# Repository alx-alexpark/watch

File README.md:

# GPS-Synchronized Watch
A nRF52840-based smartwatch that synchronizes its time from GPS satelites, featuring a waterproof enclosure and month-long battery life.

## Why I made this
Commonly used time synchronization methods such as NTP commonly used by smartwatches only provide accuracy of around 5-50ms, which is honestly not that good. GPS time is accurate to 10-50 nanoseconds, which is very good. I also care a lot about privacy so I wanted to make an air-gapped smartwatch that still is able to get very accurate time.

## Design files
[View PCB/Schematics on KiCanvas](https://kicanvas.org/?repo=https%3A%2F%2Fgithub.com%2Falx-alexpark%2Fwatch%2Ftree%2Fmain%2Fpcb) \
[View CAD on OnShape](https://cad.onshape.com/documents/4c7ff3da2943e425ef5063a9/w/a0d315951a28c31d027d9c75/e/9f56870fde0bf2563f4cad87?renderMode=0&uiState=6a2ecfbd296c1803119f765e)

## BOM
| Value | Qty | Link |
|-------|-----|------|
| DSGP.1575.18.4.A.02 | 1 | [Digikey](https://www.digikey.com/en/products/detail/taoglas-limited/DSGP-1575-18-4-A-02/8275269) |
| Adafruit Wireless Chg Module | 1 | [Digikey](https://www.adafruit.com/product/1901) |
| 100nF | 9 | [C1525](https://www.lcsc.com/product-detail/C1525.html) |
| 100pF | 1 | [C1546](https://www.lcsc.com/product-detail/C1546.html) |
| 12pF | 2 | [C1547](https://www.lcsc.com/product-detail/C1547.html) |
| 47nF | 1 | [C1622](https://www.lcsc.com/product-detail/C1622.html) |
| red | 1 | [C2286](https://www.lcsc.com/product-detail/C2286.html) |
| green | 1 | [C2297](https://www.lcsc.com/product-detail/C2297.html) |
| USBLC6-2SC6 | 1 | [C7519](https://www.lcsc.com/product-detail/C7519.html) |
| 4.7uF | 5 | [C19666](https://www.lcsc.com/product-detail/C19666.html) |
| 1.13k | 1 | [C22833](https://www.lcsc.com/product-detail/C22833.html) |
| nRF52840 | 1 | [C23186](https://www.lcsc.com/product-detail/C23186.html) |
| 100k | 1 | [C25741](https://www.lcsc.com/product-detail/C25741.html) |
| 10k | 3 | [C25744](https://www.lcsc.com/product-detail/C25744.html) |
| 1.5k | 4 | [C25867](https://www.lcsc.com/product-detail/C25867.html) |
| 22uF | 1 | [C45783](https://www.lcsc.com/product-detail/C45783.html) |
| 1uF | 5 | [C52923](https://www.lcsc.com/product-detail/C52923.html) |
| BQ24074RGT | 1 | [C54313](https://www.lcsc.com/product-detail/C54313.html) |
| RV-3028-C7 | 1 | [C3019759](https://www.lcsc.com/product-detail/C3019759.html) |
| 1A/1.8A | 1 | [C70082](https://www.lcsc.com/product-detail/C70082.html) |
| 10uH | 2 | [C88182](https://www.lcsc.com/product-detail/C88182.html) |
| 10uF | 1 | [C96446](https://www.lcsc.com/product-detail/C96446.html) |
| 15nH | 1 | [C98055](https://www.lcsc.com/product-detail/C98055.html) |
|  | 1 | [C127355](https://www.lcsc.com/product-detail/C127355.html) |
| LiPo (JST-PH Connector) | 1 | [C295747](https://www.lcsc.com/product-detail/C295747.html) |
| TPS63802DLAR | 1 | [C2845237](https://www.lcsc.com/product-detail/C2845237.html) |
| 91k | 1 | [C2906973](https://www.lcsc.com/product-detail/C2906973.html) |
| 4.12k | 2 | [C2930007](https://www.lcsc.com/product-detail/C2930007.html) |
| 511k | 1 | [C2930114](https://www.lcsc.com/product-detail/C2930114.html) |
| USB_C_Receptacle_USB2.0_14P | 1 | [C2988369](https://www.lcsc.com/product-detail/C2988369.html) |
| 1.18k | 1 | [C3016052](https://www.lcsc.com/product-detail/C3016052.html) |
| TPS2116DRL | 1 | [C3235557](https://www.lcsc.com/product-detail/C3235557.html) |
| MAX-M10S | 1 | [C4153167](https://www.lcsc.com/product-detail/C4153167.html) |
| 46.4k | 1 | [C5126026](https://www.lcsc.com/product-detail/C5126026.html) |
| 32MHz | 1 | [C5441424](https://www.lcsc.com/product-detail/C5441424.html) |
| 0.47uH | 1 | [C18221164](https://www.lcsc.com/product-detail/C18221164.html) |
| TPS7A20xxxDQN | 1 | [C46459900](https://www.lcsc.com/product-detail/C46459900.html) |

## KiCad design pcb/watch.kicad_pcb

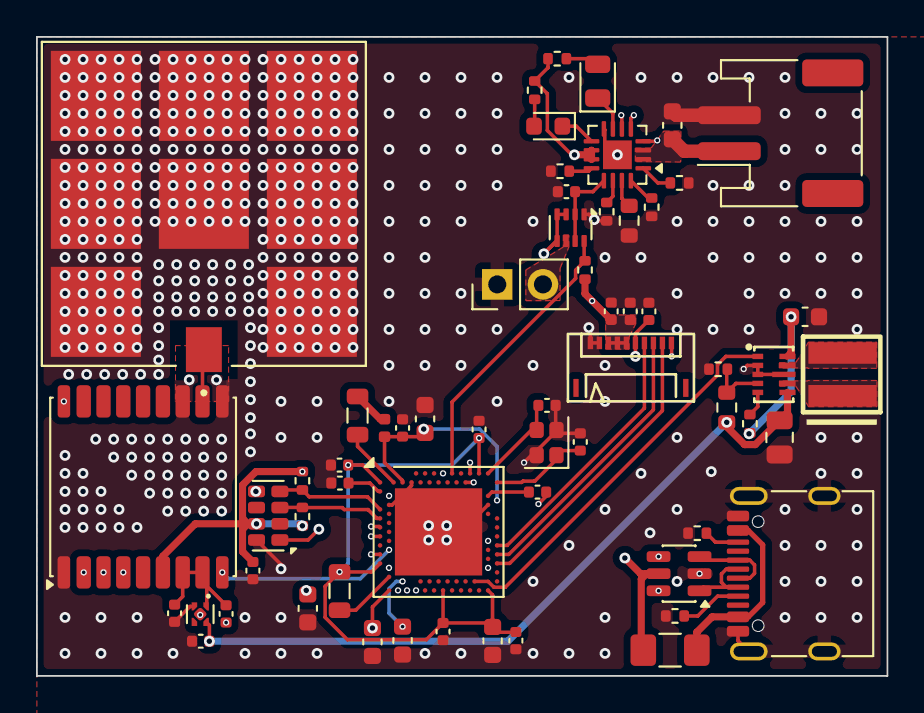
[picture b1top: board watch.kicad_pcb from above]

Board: 6 copper layers, 47.2 x 35.5 mm, 61 parts (0 on the bottom side), 59 nets.

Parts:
BT1: LiPo; JST_PH_S2B-PH-SM4-TB_1x02-1MP_P2.00mm_Horizontal
C1, C6, C7, C8, C9, C15, C25, C27, C28: 100nF; C_0402_1005Metric
C2, C10, C11, C12, C22: 4.7uF; C_0603_1608Metric
C3, C4: 12pF; C_0402_1005Metric
C5: 100pF; C_0402_1005Metric
C13, C18, C19, C21, C26: 1uF; C_0402_1005Metric
C14: 47nF; C_0603_1608Metric
C17: 10uF; C_0603_1608Metric
C20: 22uF; C_0805_2012Metric
D1: green; LED_0805_2012Metric
D2: red; LED_0603_1608Metric
DS1: 5034801000
E1: DSGP.1575.18.4.A.02; XCVR_DSGP.1575.18.4.A.02
F1: 1A/1.8A; Fuse_1206_3216Metric_Pad1.42x1.75mm_HandSolder
J1: USB_C_Receptacle_USB2.0_14P; USB_C_Receptacle_G-Switch_GT-USB-7010ASV
J2: Adafruit Wireless Chg Module; PinHeader_1x02_P2.54mm_Vertical
L1, L2: 10uH; L_0805_2012Metric
L3: 15nH; L_0402_1005Metric
L4: 0.47uH; XFL4015-471MEC
R1, R2: 4.12k; R_0402_1005Metric
R3: 511k; R_0603_1608Metric
R4: 91k; R_0402_1005Metric
R5: 100k; R_0402_1005Metric
R6: 1.18k; R_0402_1005Metric
R7, R8, R11, R12: 1.5k; R_0402_1005Metric
R9: 1.13k; R_0603_1608Metric
R10: 46.4k; R_0402_1005Metric
R15, R16, R17: 10k; R_0402_1005Metric
U1: nRF52840; Nordic_AQFN-73-1EP_7x7mm_P0.5mm
U2: USBLC6-2SC6; SOT-23-6
U3: MAX-M10S; ublox_MAX
U4: TPS63802DLAR
U5: TPS7A20xxxDQN; Texas_X2SON-4_1x1mm_P0.65mm
U6: BQ24074RGT; VQFN-16-1EP_3x3mm_P0.5mm_EP1.6x1.6mm
U8: RV-3028-C7; MicroCrystal_C7_SON-8_1.5x3.2mm_P0.9mm
U9: TPS2116DRL; SOT-583-8
Y1: 32MHz; Crystal_SMD_2016-4Pin_2.0x1.6mm

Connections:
+3V0_GPS: C15.1, C19.1, U3.7 (VCC_IO), U3.8 (VCC), U5.1 (OUT)
+3V3: C26.1, C27.1, C28.1, DS1.3 (EXTMODE), DS1.4 (VDD), DS1.5 (VDDA), R15.1, R16.1, R17.1, U3.6 (V_BCKP), U8.7 (VDD)
+3V3_ALT: C18.1, C20.1, R3.1, U4.6 (VOUT), U5.4 (IN)
+BATT: C11.1, C17.1, R5.1, R11.2, R12.2, U1.Y2 (VDDH), U4.10 (VIN), U6.10 (OUT), U6.11 (OUT)
/mcu/D+: U1.AD6 (D+), U2.4 (I/O2)
/mcu/D-: U1.AD4 (D-), U2.6 (I/O1)
/mcu/DEC4: C13.1, C14.1, L3.1, U1.B5 (DEC4), U1.E24 (DEC6)
/mcu/VDD_nRF: C1.1, C6.1, C8.1, C9.1, C10.1, L1.1, U1.A22 (VDD), U1.AD14 (VDD), U1.AD23 (VDD), U1.B1 (VDD), U1.W1 (VDD)
GND: BT1.2 (-), C1.2, C2.2, C3.1, C4.1, C5.2, C6.2, C7.2, C8.2, C9.2, C10.2, C11.2, C12.2, C13.2, C14.2, C15.2, C17.2, C18.2, C20.2, C21.2, C22.2, C25.2, C26.2, C27.2, C28.2, DS1.1 (VSSA), DS1.2 (VSS), E1.2, E1.3, E1.4, E1.5, E1.6, E1.7, E1.8, E1.9, J1.A1 (GND), J1.A12 (GND), J1.B1 (GND), J1.B12 (GND), J1.SH (SHIELD), J2.1, R1.2, R2.2, R4.2, R6.1, R7.1, R8.1, R9.1, R10.2, U1.B7 (VSS), U1.EP (VSS), U1.F2 (XL2/P0.01), U1.F23 (VSS_PA), U2.2 (GND), U3.1 (GND), U3.10 (GND), U3.12 (GND), U4.2 (MODE), U4.3 (AGND), U4.8 (GND), U5.2 (GND), U6.8 (VSS), U6.17 (VSS), U8.5 (VSS), U8.8 (EVI), U9.1 (GND), Y1.2 (G), Y1.4 (G)
LF_EXT_CLK: U1.D2 (XL1/P0.00), U8.1 (CLKOUT)
unnamed: BT1.1 (+), C22.1, U6.2 (BAT), U6.3 (BAT)
unnamed: C19.2, U5.5 (Pad)
unnamed: D1.2 (A), R11.1
unnamed: D1.1 (K), U6.7 (~PGOOD)
unnamed: D2.2 (A), R12.1
unnamed: D2.1 (K), U6.9 (~CHG)
unnamed: F1.1, J1.A4 (VBUS), J1.A9 (VBUS), J1.B4 (VBUS), J1.B9 (VBUS)
unnamed: J1.A5 (CC1), R1.1
unnamed: J1.B5 (CC2), R2.1
unnamed: J1.A6 (D+), J1.B6 (D+), U2.3 (I/O2)
unnamed: J1.A7 (D-), J1.B7 (D-), U2.1 (I/O1)
unnamed: J2.2, U9.6 (VIN2)
unnamed: L2.1, L3.2
unnamed: L2.2, U1.B3 (DCC)
unnamed: L1.2, U1.AB2 (DCCH)
unnamed: C7.1, U1.C1 (DEC1)
unnamed: C5.1, U1.D23 (DEC3)
unnamed: C2.1, U1.AC5 (DECUSB)
unnamed: C3.2, U1.B24 (XC1), Y1.1
unnamed: C4.2, U1.A23 (XC2), Y1.3
unnamed: E1.1, U3.11 (RF_IN)
unnamed: R3.2, R4.1, U4.4 (FB)
unnamed: L4.2, U4.9 (L1)
unnamed: L4.1, U4.7 (L2)
unnamed: R5.2, U4.5 (PG)
unnamed: R7.2, U6.12 (ILIM)
unnamed: R8.2, U6.16 (ISET)
unnamed: R9.2, U6.15 (ITERM)
unnamed: R6.2, U6.14 (TMR)
unnamed: R10.1, U6.1 (TS)
P0.04: R15.2, U1.J1 (AIN2/P0.04), U8.3 (SCL)
P0.06: U1.L1 (P0.06), U3.18 (~SAFEBOOT)
P0.08: U1.N1 (P0.08), U3.2 (TXD)
P0.11: U1.T2 (TRACEDATA2/P0.11), U3.9 (~RESET)
P0.12: U1.U1 (TRACEDATA1/P0.12), U3.3 (RXD)
P0.25: U1.AC21 (P0.25), U4.1 (EN)
P0.26: R16.2, U1.G1 (P0.26), U8.4 (SDA)
P1.01: DS1.10 (SCLK), U1.Y23 (P1.01)
P1.02: DS1.9 (SI), U1.W24 (P1.02)
P1.04: DS1.8 (SCS), U1.U24 (P1.04)
P1.06: DS1.7 (EXTCOMIN), U1.R24 (P1.06)
P1.07: C25.1, DS1.6 (DISP), U1.P23 (P1.07)
P1.10: U1.A20 (P1.10), U6.5 (EN2)
P1.11: U1.B19 (P1.11), U6.4 (~CE)
P1.13: R17.2, U1.A16 (P1.13), U9.8 (ST)
P1.15: U1.A14 (P1.15), U6.6 (EN1)
TIMEPULSE: U1.AD8 (P0.13), U3.4 (TIMEPULSE)
VBUS: C12.1, F1.2, U1.AD2 (VBUS), U2.5 (VBUS), U9.3 (VIN1), U9.4 (PR1), U9.5 (MODE)
V_CHARGE: C21.1, U6.13 (IN), U9.2 (VOUT), U9.7 (VOUT)

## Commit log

2026-05-31 sussy
2026-06-01 stuff
2026-06-05 sus commit
2026-06-05 sus2
2026-06-05 fix symbols getting absolutely goofed up
2026-06-05 del oled.sch
2026-06-05 fix more stuffies
2026-06-05 ALMOST done with parts purgatory
2026-06-07 done for the day
2026-06-08 amogus
2026-06-08 change to 4layer
2026-06-10 starting le leyout
2026-06-13 mogus
2026-06-13 almost done?
2026-06-14 SUS!!
